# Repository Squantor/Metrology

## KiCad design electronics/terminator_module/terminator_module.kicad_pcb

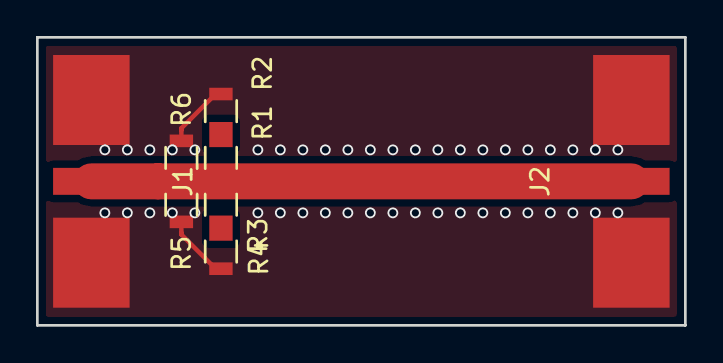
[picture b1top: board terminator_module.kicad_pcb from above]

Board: 2 copper layers, 36.0 x 16.0 mm, 8 parts (0 on the bottom side), 4 nets.

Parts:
J1, J2: Coax; coax_edge_1.5_center_5_side
R1, R2, R3, R4, R5, R6: R; R_0805

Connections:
GND: J1.1, J2.1, R2.2, R4.2, R5.2, R6.2
unnamed: J1.2, J2.2, R1.1, R3.1, R5.1, R6.1
unnamed: R1.2, R2.1
unnamed: R3.2, R4.1

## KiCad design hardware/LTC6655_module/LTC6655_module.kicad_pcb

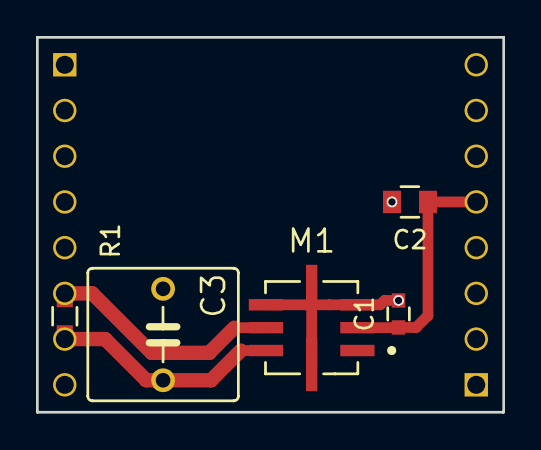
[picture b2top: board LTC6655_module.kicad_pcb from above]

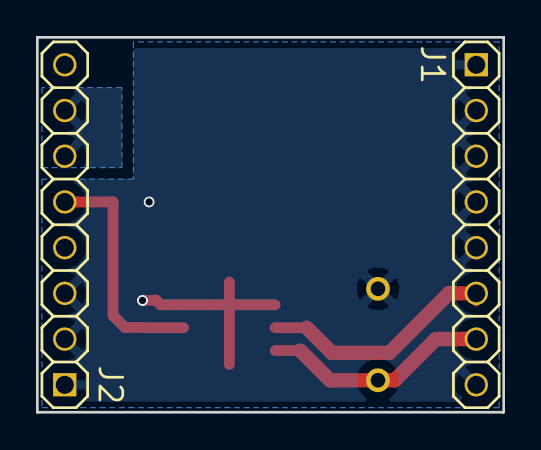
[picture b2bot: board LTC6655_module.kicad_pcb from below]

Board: 2 copper layers, 25.9 x 20.8 mm, 7 parts (2 on the bottom side), 5 nets.

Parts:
C1: 1u; C_0603
C2: 10n; C_0805
C3: 6.8u; C050-085X075
J1, J2: PINS_1X8; Header-0254-1X08-H010
M1: LTC6655LS8; LS8_ELONG
R1: 0; R_0603

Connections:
GND: C1.2, C2.2, C3.2, J1.1, J1.2, J1.3, J1.4, J1.5, J1.8, J2.1, J2.2, J2.3, M1.3, M1.4, M1.5, M1.8
HeaterGround: J2.6, J2.7
Sense: J1.6, M1.6, R1.1
Vin: C1.1, C2.1, J2.5, M1.2
Vref: C3.1, J1.7, M1.7, R1.2

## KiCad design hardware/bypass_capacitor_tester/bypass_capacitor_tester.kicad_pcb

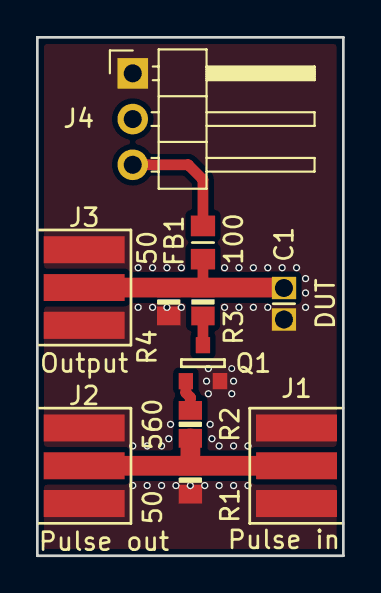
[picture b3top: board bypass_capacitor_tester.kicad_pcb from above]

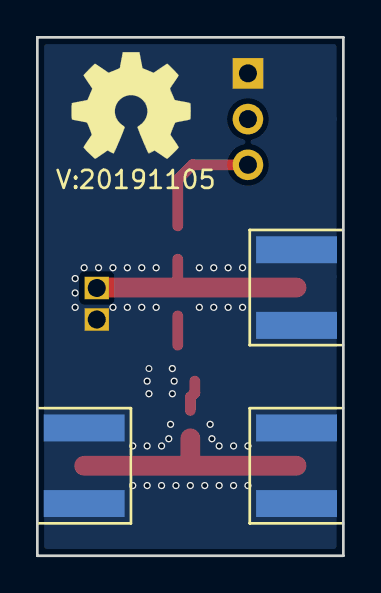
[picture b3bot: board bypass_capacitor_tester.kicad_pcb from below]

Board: 2 copper layers, 17.0 x 28.8 mm, 13 parts (2 on the bottom side), 6 nets.

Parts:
C1: DUT; C_TH+0805+0603+0402
FB1: Ferrite_Bead; C_0805+0603
J1: Pulse in; SMA_edge_6mm2
J2: Pulse out; SMA_edge_6mm2
J3: Output; SMA_edge_6mm2
J4: Conn_01x02; PinHeader_1x03_P2.54mm_Horizontal
N1: OHWLOGO; OSHW-Symbol_6.7x6mm_SilkScreen
N2: 20191105; Label_version
Q1: MMBT2369AL; SOT23-3
R1, R4: 50; R_0805+0603
R2: 560; R_0805+0603
R3: 100; R_0805+0603

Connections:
/A_WAVEFORM: J1.1, J2.1, R1.1, R2.2
/B_WAVEFORM: C1.1, FB1.2, J3.1, R3.1, R4.1
GND: C1.2, J1.2, J2.2, J3.2, J4.1, Q1.2, R1.2, R4.2
unnamed: Q1.1, R2.1
unnamed: Q1.3, R3.2
VDD: FB1.1, J4.3

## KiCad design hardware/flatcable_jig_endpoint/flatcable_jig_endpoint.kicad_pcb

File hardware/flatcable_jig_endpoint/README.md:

# Flatcable Jig endpoint
Flatcables are a bit more convienient (and cheaper) to link up test jigs or projects together. This is an initial test of this and serves as a endpoint for these cables.
## Work
Current tasklist:
* schematic entry (Done)
* PCB layout (Done)
* Review with one night in between (TODO)
* Produce at [OSHPARK](https://oshpark.com/) (TODO)
* Assemble (TODO)
* Test & characterise (TODO)
* update Readme.md with pictures and BOM (TODO)
## BOM
Using extruded aluminium miniboxes, 25mm wide 50mm long. 

Get them from your favorite chinese material vendor, I usually get them in bulk from ebay. They accept a 22mm wide in their slots.
## Pictures

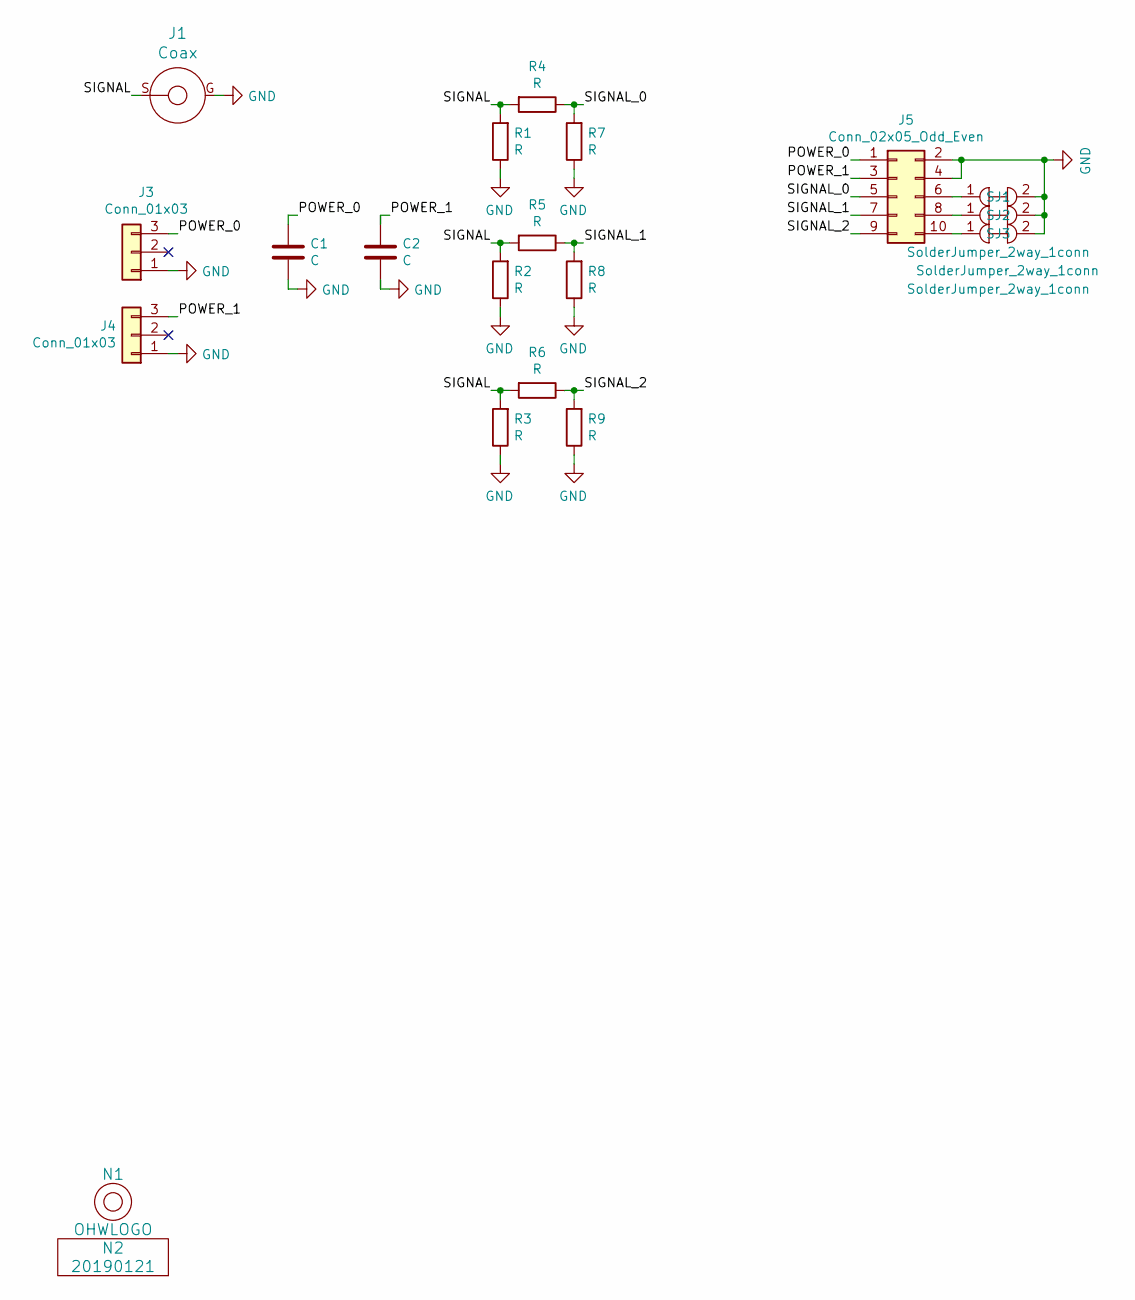
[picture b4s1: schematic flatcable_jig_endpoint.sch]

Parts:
C1, C2: C; C_0805
J1: Coax; Conn_BNC_RightAngle_TH
J3, J4: Conn_01x03; Molex_KK-254_AE-6410-03A_1x03_P2.54mm_Vertical
J5: Conn_02x05_Odd_Even; Header-0254-2X05-H010
N1: OHWLOGO; OSHW-Symbol_6.7x6mm_SilkScreen
N2: 20190121; Label_version
R1, R2, R3, R4, R5, R6, R7, R8, R9: R; R_0603_hand
SJ1, SJ2, SJ3: SolderJumper_2way_1conn; solder_jumper_2way_conn

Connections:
/POWER_0: C1.1, J3.3, J5.1
/POWER_1: C2.1, J4.3, J5.3
/SIGNAL: J1.S, R1.2, R2.2, R3.2, R4.2, R5.2, R6.2
/SIGNAL_0: J5.5, R4.1, R7.2
/SIGNAL_1: J5.7, R5.1, R8.2
/SIGNAL_2: J5.9, R6.1, R9.2
GND: C1.2, C2.2, J1.G, J3.1, J4.1, J5.2, J5.4, R1.1, R2.1, R3.1, R7.1, R8.1, R9.1, SJ1.2, SJ2.2, SJ3.2
unnamed: J5.6, SJ1.1
unnamed: J5.8, SJ2.1
unnamed: J5.10, SJ3.1

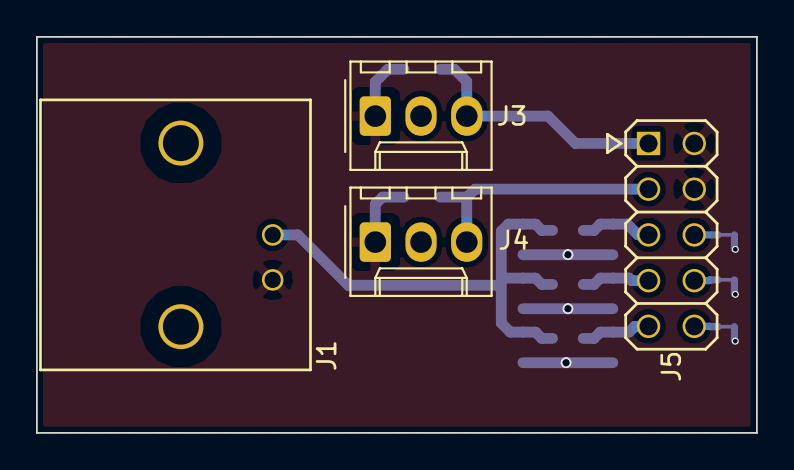
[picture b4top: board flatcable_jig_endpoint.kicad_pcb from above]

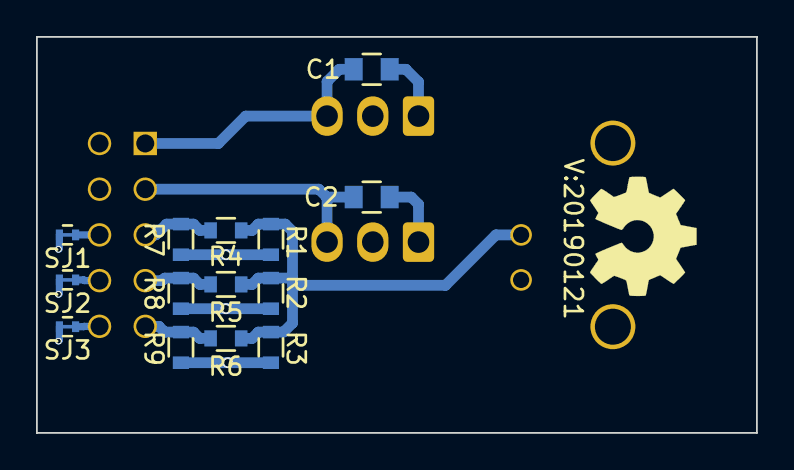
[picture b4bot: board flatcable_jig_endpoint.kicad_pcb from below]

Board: 2 copper layers, 40.0 x 22.0 mm, 20 parts (15 on the bottom side), 10 nets.

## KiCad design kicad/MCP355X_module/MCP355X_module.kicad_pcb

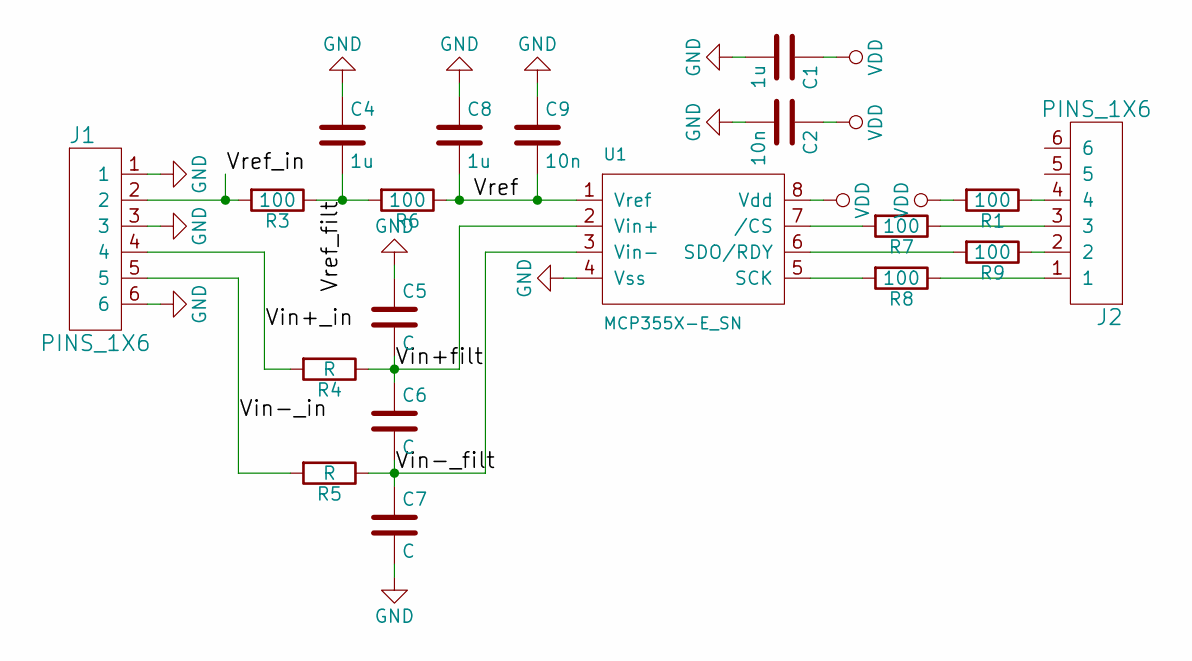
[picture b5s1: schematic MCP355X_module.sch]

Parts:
C1: 1u; C_0805
C2, C9: 10n; C_0603
C4, C8: 1u; RCL-C025-050X050
C5, C6, C7: C; C_0805
J1, J2: PINS_1X6; Header-2.54-1X06-H0.8
R1, R3, R6, R7, R8, R9: 100; R_0603
R4, R5: R; R_0603
U1: MCP355X-E_SN; SN8-(SOIC8)

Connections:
/Vin+_in: J1.4, R4.2
/Vin+filt: C5.2, C6.1, R4.1, U1.2 (Vin+)
/Vin-_filt: C6.2, C7.1, R5.1, U1.3 (Vin-)
/Vin-_in: J1.5, R5.2
/Vref: C8.2, C9.2, R6.1, U1.1 (Vref)
/Vref_filt: C4.2, R3.1, R6.2
/Vref_in: J1.2, R3.2
GND: C1.2, C2.2, C4.1, C5.1, C7.2, C8.1, C9.1, J1.1, J1.3, J1.6, U1.4 (Vss)
unnamed: J2.1, R8.1
unnamed: J2.2, R9.1
unnamed: J2.3, R7.1
unnamed: J2.4, R1.1
unnamed: R7.2, U1.7 (/CS)
unnamed: R8.2, U1.5 (SCK)
unnamed: R9.2, U1.6 (SDO/RDY)
VDD: C1.1, C2.1, R1.2, U1.8 (Vdd)

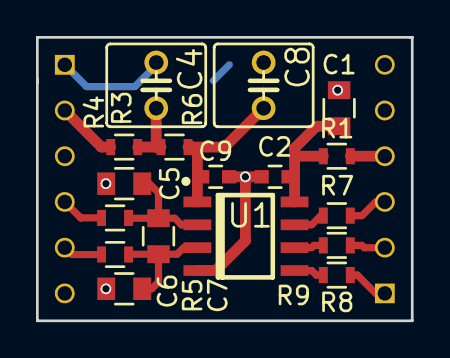
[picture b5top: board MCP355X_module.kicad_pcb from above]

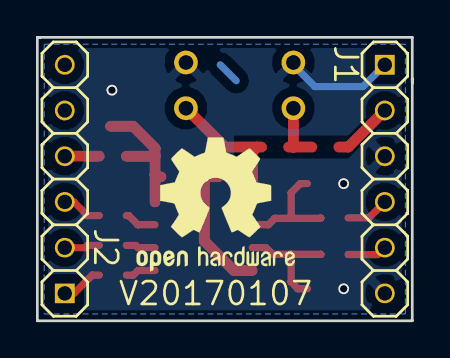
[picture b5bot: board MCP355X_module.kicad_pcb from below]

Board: 2 copper layers, 20.8 x 15.7 mm, 19 parts (2 on the bottom side), 16 nets.
